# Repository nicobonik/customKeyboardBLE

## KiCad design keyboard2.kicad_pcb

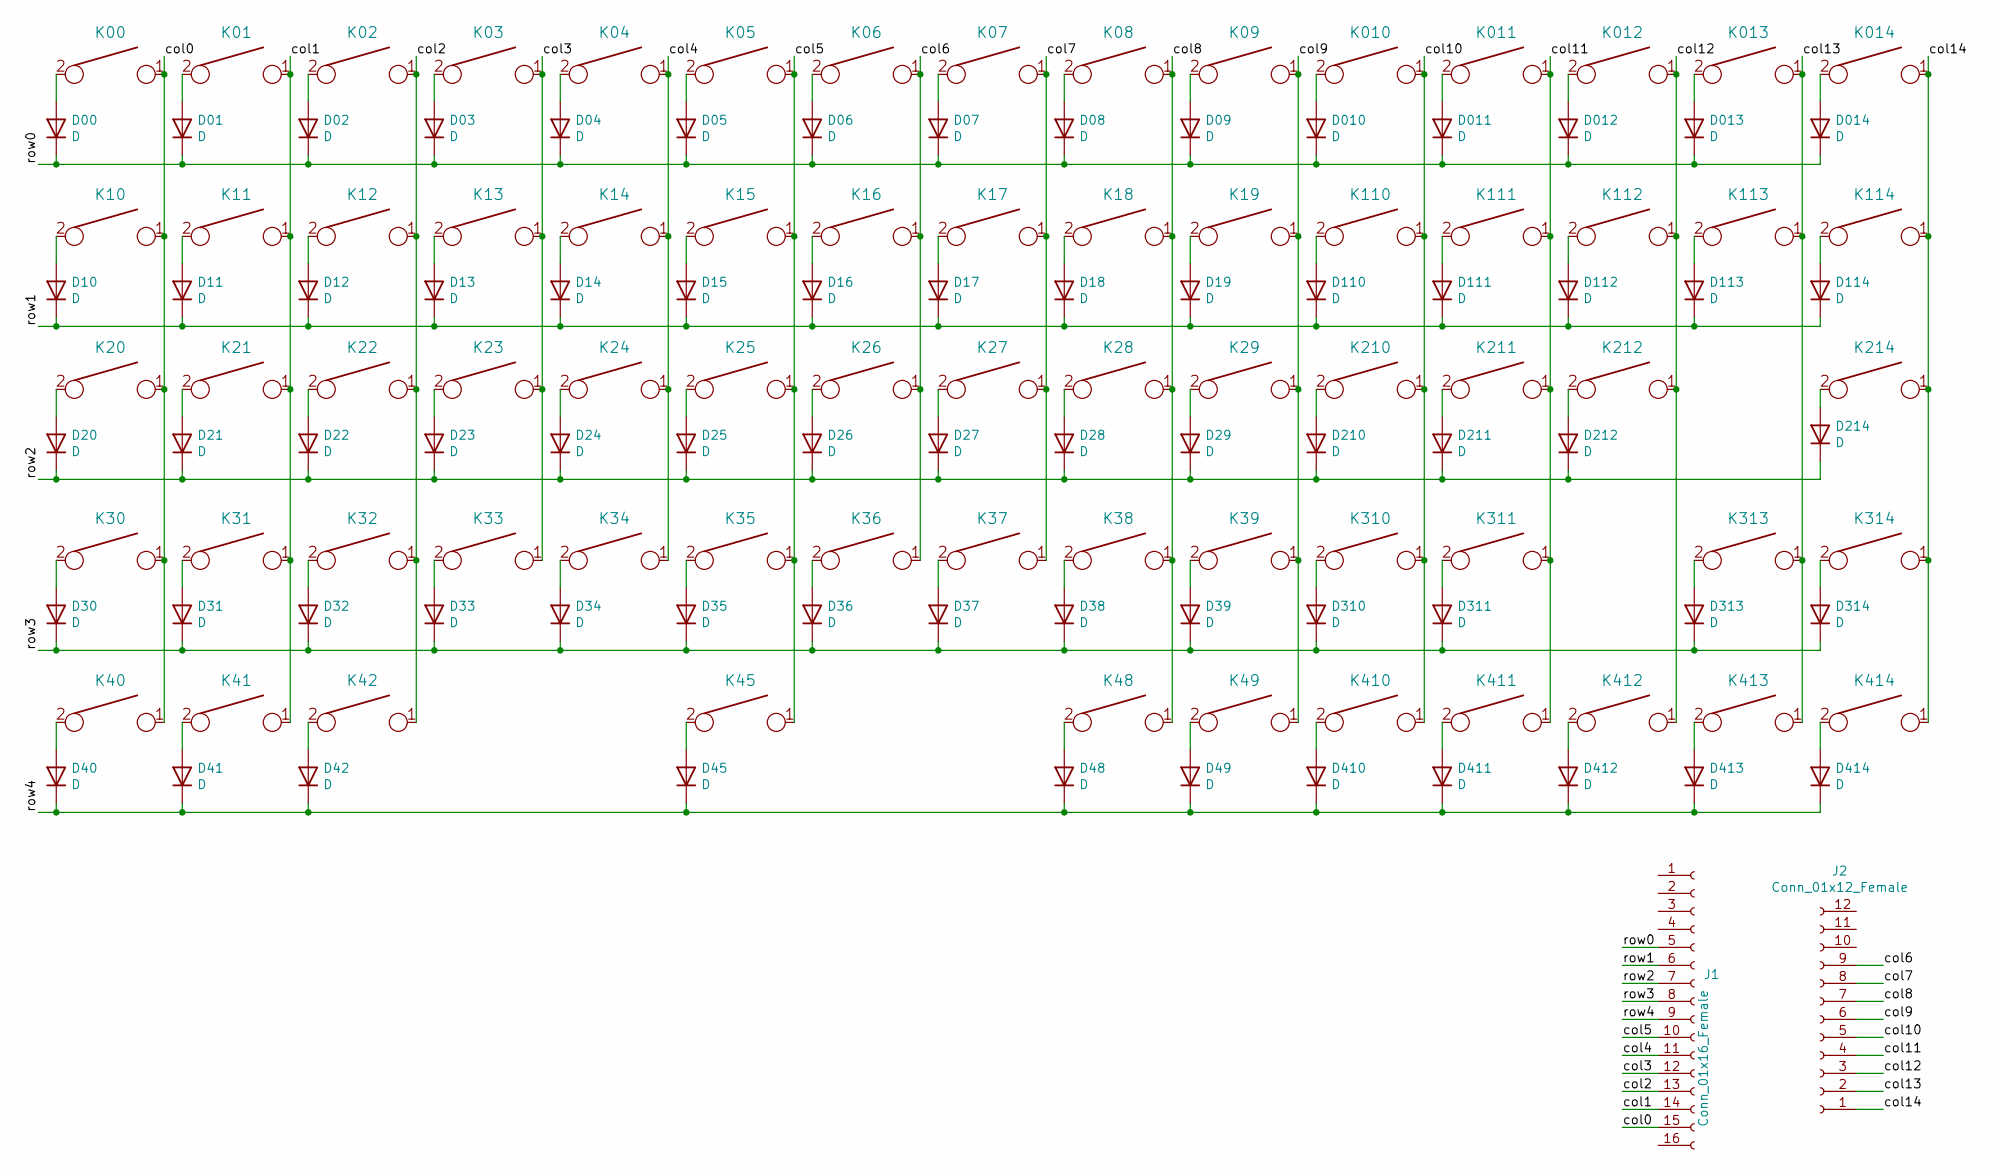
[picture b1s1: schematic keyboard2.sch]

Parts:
D00, D01, D02, D03, D04, D05, D06, D07, D08, D09, D10, D010, D011, D11, D012, D12, D013, D13, D014, D14, D15, D16, D17, D18, D19, D20, D21, D22, D23, D24, D25, D26, D27, D28, D29, D30, D31, D32, D33, D34, D35, D36, D37, D38, D39, D40, D41, D42, D45, D48, D49, D110, D111, D112, D113, D114, D210, D211, D212, D214, D310, D311, D313, D314, D410, D411, D412, D413, D414: D; D_SOD-123
J1: Conn_01x16_Female; PinHeader_1x16_P2.54mm_Vertical
J2: Conn_01x12_Female; PinHeader_1x12_P2.54mm_Vertical
K00, K01, K02, K03, K04, K05, K06, K07, K08, K09, K010, K011, K11, K012, K12, K13, K014, K14, K15, K16, K17, K18, K19, K21, K22, K23, K24, K25, K26, K27, K28, K29, K31, K32, K33, K34, K35, K36, K37, K38, K39, K110, K111, K112, K114, K210, K211, K214, K310, K313, K314, K412, K413, K414: KEYSW; SW_Cherry_MX_1.00u_PCB
K10, K113: KEYSW; SW_Cherry_MX_1.50u_PCB
K013: KEYSW; SW_Cherry_MX_2.00u_PCB
K20: KEYSW; SW_Cherry_MX_1.75u_PCB
K30, K212: KEYSW; SW_Cherry_MX_2.25u_PCB
K40, K41, K42, K48, K49, K410, K411: KEYSW; SW_Cherry_MX_1.25u_PCB
K45: KEYSW; SW_Cherry_MX_6.25u_PCB
K311: KEYSW; SW_Cherry_MX_2.75u_PCB

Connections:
/col0: J1.15, K00.1, K10.1, K20.1, K30.1, K40.1
/col1: J1.14, K01.1, K11.1, K21.1, K31.1, K41.1
/col2: J1.13, K02.1, K12.1, K22.1, K32.1, K42.1
/col3: J1.12, K03.1, K13.1, K23.1, K33.1
/col4: J1.11, K04.1, K14.1, K24.1, K34.1
/col5: J1.10, K05.1, K15.1, K25.1, K35.1, K45.1
/col6: J2.9, K06.1, K16.1, K26.1, K36.1
/col7: J2.8, K07.1, K17.1, K27.1, K37.1
/col8: J2.7, K08.1, K18.1, K28.1, K38.1, K48.1
/col9: J2.6, K09.1, K19.1, K29.1, K39.1, K49.1
/col10: J2.5, K010.1, K110.1, K210.1, K310.1, K410.1
/col11: J2.4, K011.1, K111.1, K211.1, K311.1, K411.1
/col12: J2.3, K012.1, K112.1, K212.1, K412.1
/col13: J2.2, K013.1, K113.1, K313.1, K413.1
/col14: J2.1, K014.1, K114.1, K214.1, K314.1, K414.1
/row0: D00.1 (K), D01.1 (K), D02.1 (K), D03.1 (K), D04.1 (K), D05.1 (K), D06.1 (K), D07.1 (K), D08.1 (K), D09.1 (K), D010.1 (K), D011.1 (K), D012.1 (K), D013.1 (K), D014.1 (K), J1.5
/row1: D10.1 (K), D11.1 (K), D12.1 (K), D13.1 (K), D14.1 (K), D15.1 (K), D16.1 (K), D17.1 (K), D18.1 (K), D19.1 (K), D110.1 (K), D111.1 (K), D112.1 (K), D113.1 (K), D114.1 (K), J1.6
/row2: D20.1 (K), D21.1 (K), D22.1 (K), D23.1 (K), D24.1 (K), D25.1 (K), D26.1 (K), D27.1 (K), D28.1 (K), D29.1 (K), D210.1 (K), D211.1 (K), D212.1 (K), D214.1 (K), J1.7
/row3: D30.1 (K), D31.1 (K), D32.1 (K), D33.1 (K), D34.1 (K), D35.1 (K), D36.1 (K), D37.1 (K), D38.1 (K), D39.1 (K), D310.1 (K), D311.1 (K), D313.1 (K), D314.1 (K), J1.8
/row4: D40.1 (K), D41.1 (K), D42.1 (K), D45.1 (K), D48.1 (K), D49.1 (K), D410.1 (K), D411.1 (K), D412.1 (K), D413.1 (K), D414.1 (K), J1.9
unnamed: D00.2 (A), K00.2
unnamed: D01.2 (A), K01.2
unnamed: D02.2 (A), K02.2
unnamed: D03.2 (A), K03.2
unnamed: D04.2 (A), K04.2
unnamed: D05.2 (A), K05.2
unnamed: D06.2 (A), K06.2
unnamed: D07.2 (A), K07.2
unnamed: D08.2 (A), K08.2
unnamed: D09.2 (A), K09.2
unnamed: D010.2 (A), K010.2
unnamed: D10.2 (A), K10.2
unnamed: D11.2 (A), K11.2
unnamed: D011.2 (A), K011.2
unnamed: D12.2 (A), K12.2
unnamed: D012.2 (A), K012.2
unnamed: D013.2 (A), K013.2
unnamed: D13.2 (A), K13.2
unnamed: D014.2 (A), K014.2
unnamed: D14.2 (A), K14.2
unnamed: D15.2 (A), K15.2
unnamed: D16.2 (A), K16.2
unnamed: D17.2 (A), K17.2
unnamed: D18.2 (A), K18.2
unnamed: D19.2 (A), K19.2
unnamed: D20.2 (A), K20.2
unnamed: D21.2 (A), K21.2
unnamed: D22.2 (A), K22.2
unnamed: D23.2 (A), K23.2
unnamed: D24.2 (A), K24.2
unnamed: D25.2 (A), K25.2
unnamed: D26.2 (A), K26.2
unnamed: D27.2 (A), K27.2
unnamed: D28.2 (A), K28.2
unnamed: D29.2 (A), K29.2
unnamed: D30.2 (A), K30.2
unnamed: D31.2 (A), K31.2
unnamed: D32.2 (A), K32.2
unnamed: D33.2 (A), K33.2
unnamed: D34.2 (A), K34.2
unnamed: D35.2 (A), K35.2
unnamed: D36.2 (A), K36.2
unnamed: D37.2 (A), K37.2
unnamed: D38.2 (A), K38.2
unnamed: D39.2 (A), K39.2
unnamed: D40.2 (A), K40.2
unnamed: D41.2 (A), K41.2
unnamed: D42.2 (A), K42.2
unnamed: D45.2 (A), K45.2
unnamed: D48.2 (A), K48.2
unnamed: D49.2 (A), K49.2
unnamed: D110.2 (A), K110.2
unnamed: D111.2 (A), K111.2
unnamed: D112.2 (A), K112.2
unnamed: D113.2 (A), K113.2
unnamed: D114.2 (A), K114.2
unnamed: D210.2 (A), K210.2
unnamed: D211.2 (A), K211.2
unnamed: D212.2 (A), K212.2
unnamed: D214.2 (A), K214.2
unnamed: D310.2 (A), K310.2
unnamed: D311.2 (A), K311.2
unnamed: D313.2 (A), K313.2
unnamed: D314.2 (A), K314.2
unnamed: D410.2 (A), K410.2
unnamed: D411.2 (A), K411.2
unnamed: D412.2 (A), K412.2
unnamed: D413.2 (A), K413.2
unnamed: D414.2 (A), K414.2

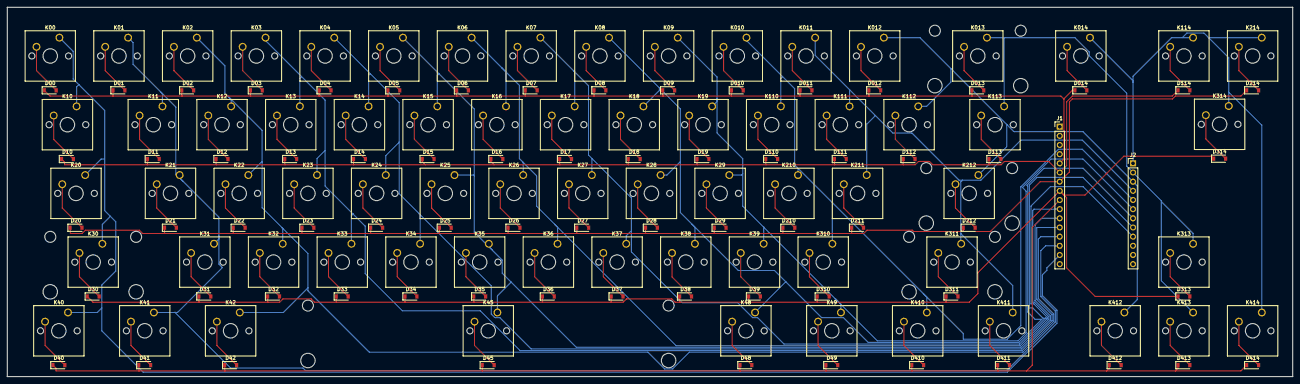
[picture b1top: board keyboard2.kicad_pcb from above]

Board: 2 copper layers, 356.4 x 102.4 mm, 140 parts (0 on the bottom side), 89 nets.

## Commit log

2020-08-06 finished basic layout iteration 1
2020-08-06 start work on traces
2020-08-06 finished row traces
2020-08-06 used the wrong diodes, have to redo all traces
2020-08-06 finished alphanumeric placement on pcb
2020-08-06 finished row wiring with new components
2020-08-06 rev1 complete
